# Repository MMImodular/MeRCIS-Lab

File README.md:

# MeRCIS Lab
##### Contributors: Matt Gaines, Joe Cressman, Jason Paximadas
___
This repository will be used to keep files up to date without dealing with Google Drive permissions.
The primary use case for now is maintaining a standard Eagle Library for future designs, but more will appear in time.

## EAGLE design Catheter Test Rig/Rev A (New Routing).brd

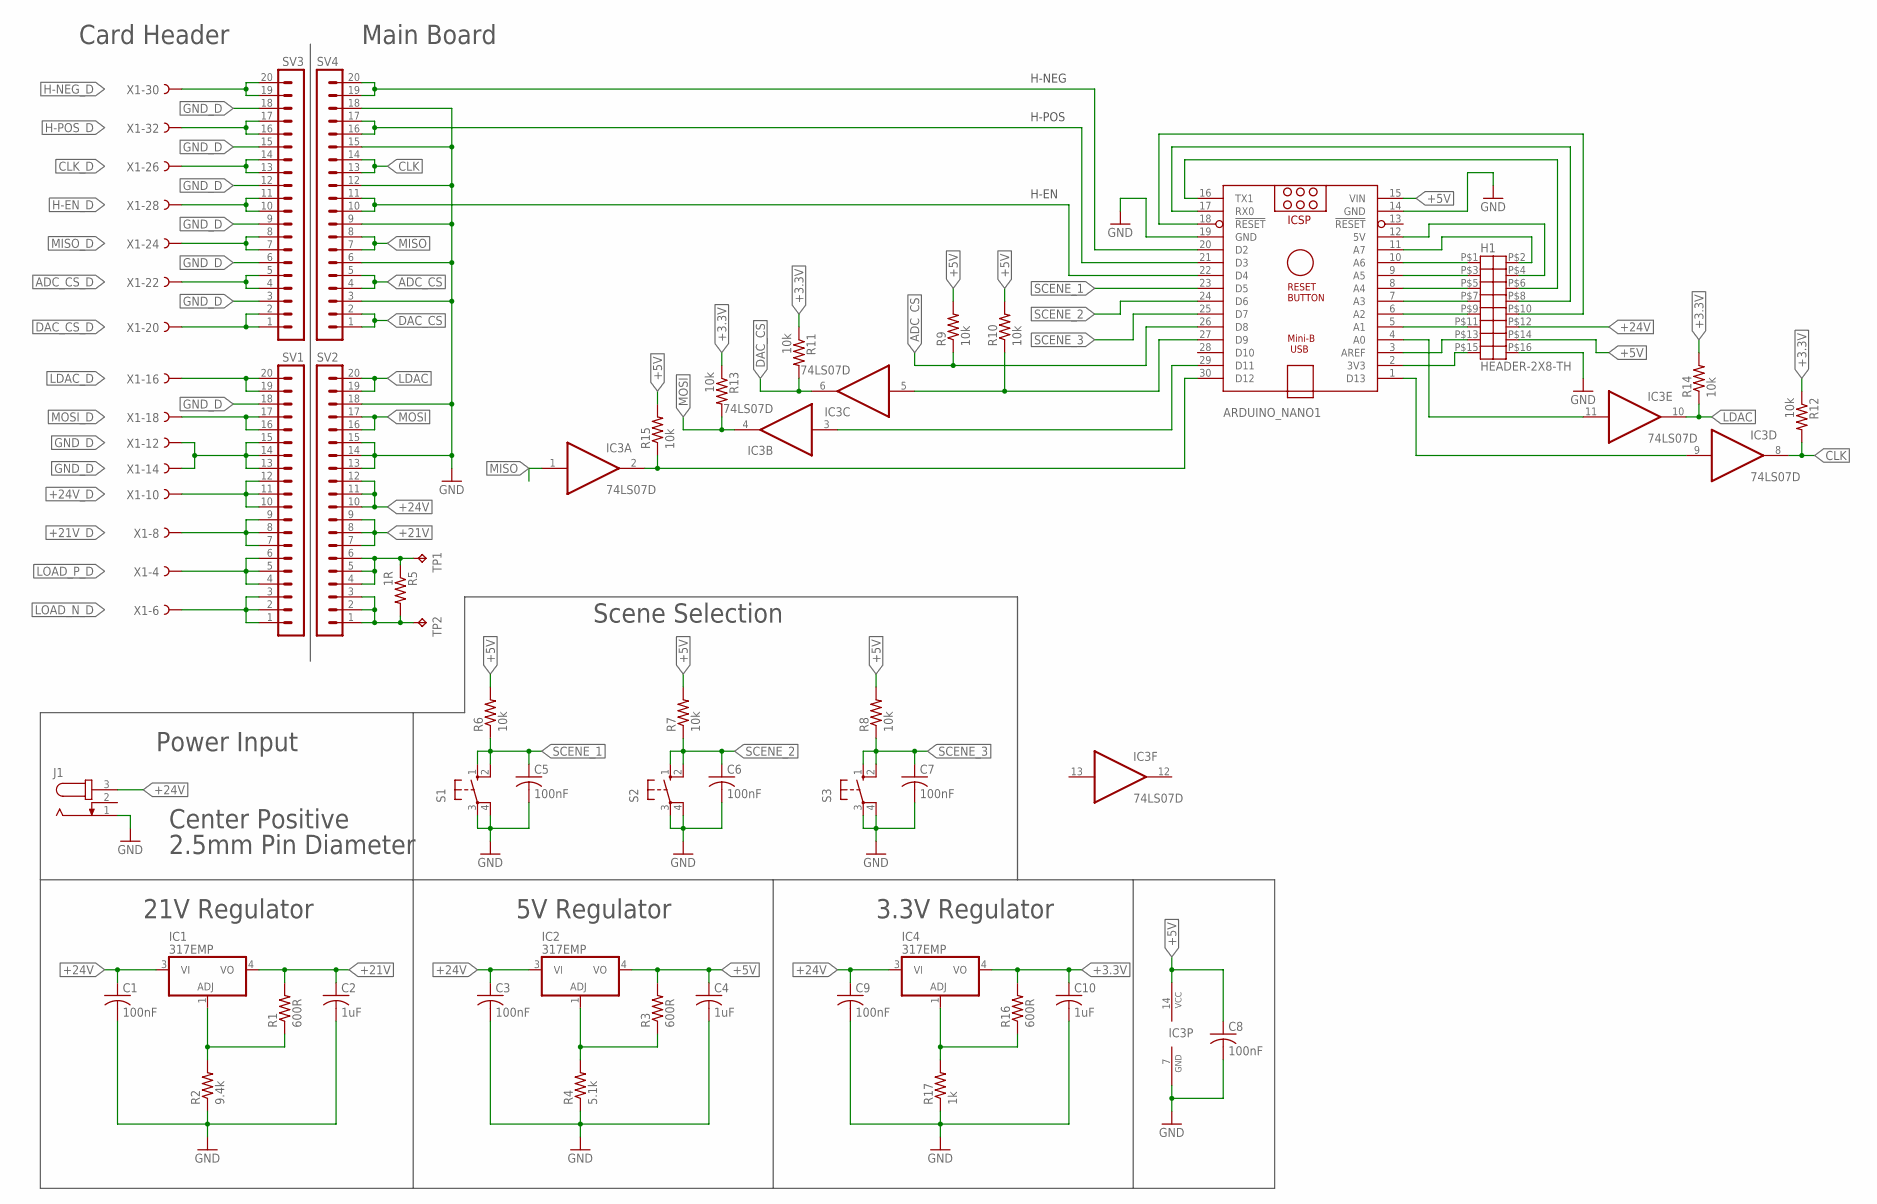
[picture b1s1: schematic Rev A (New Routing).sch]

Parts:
ARDUINO_NANO1: ARDUINO_NANO
C1, C3, C5, C6, C7, C8, C9: 100nF; C0603
C2, C4, C10: 1uF; C1206
H1: HEADER-2X8-TH
IC1, IC2, IC4: 317EMP; SOT223
IC3: 74LS07D; SO14
J1: JACK-PLUG1; SPC4078
R1, R3, R16: 600R; R0603
R2: 9.4k; R0603
R4: 5.1k; R0603
R5: 1R; R1206
R6, R7, R8, R9, R10, R11, R12, R13, R14, R15: 10k; R0603
R17: 1k; R0603
S1, S2, S3: 10-XX; B3F-10XX
SV1, SV3: MA20-1
SV2, SV4: MA20-1W
TP1, TP2: TPB2,54; B2,54
X1: FH15

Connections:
+3.3V: C10.1, IC4.4 (VO), R11.1, R12.1, R13.1, R14.2, R16.2
+5V: ARDUINO_NANO1.15 (VIN), C4.1, C8.1, H1.P$14, IC2.4 (VO), IC3.14 (VCC), R3.2, R6.2, R7.2, R8.2, R9.2, R10.2, R15.2
+21V: C2.1, IC1.4 (VO), R1.2, SV2.7, SV2.8, SV2.9
+21V_D: SV1.7, SV1.8, SV1.9, X1.8
+24V: C1.1, C3.1, C9.1, H1.P$12, IC1.3 (VI), IC2.3 (VI), IC4.3 (VI), J1.3, SV2.10, SV2.11, SV2.12
+24V_D: SV1.10, SV1.11, SV1.12, X1.10
ADC_CS: ARDUINO_NANO1.26 (D8), R9.1, SV4.4, SV4.5
ADC_CS_D: SV3.4, SV3.5, X1.22
CLK: IC3.8 (O), R12.2, SV4.13, SV4.14
CLK_D: SV3.13, SV3.14, X1.26
DAC_CS: IC3.6 (O), R11.2, SV4.1, SV4.2
DAC_CS_D: SV3.1, SV3.2, X1.20
GND: ARDUINO_NANO1.14 (GND), ARDUINO_NANO1.19 (GND), C1.2, C2.2, C3.2, C4.2, C5.2, C6.2, C7.2, C8.2, C9.2, C10.2, H1.P$16, IC3.7 (GND), J1.1, R2.1, R4.1, R17.1, S1.3, S1.4 (P1), S2.3, S2.4 (P1), S3.3, S3.4 (P1), SV2.13, SV2.14, SV2.15, SV2.18, SV4.3, SV4.6, SV4.9, SV4.12, SV4.15, SV4.18
GND_D: SV1.13, SV1.14, SV1.15, SV1.18, SV3.3, SV3.6, SV3.9, SV3.12, SV3.15, SV3.18, X1.12, X1.14
H-EN_D: SV3.10, SV3.11, X1.28
H-NEG_D: SV3.19, SV3.20, X1.30
H-POS_D: SV3.16, SV3.17, X1.32
LDAC: IC3.10 (O), R14.1, SV2.19, SV2.20
LDAC_D: SV1.19, SV1.20, X1.16
LOAD_N_D: SV1.1, SV1.2, SV1.3, X1.6
LOAD_P_D: SV1.4, SV1.5, SV1.6, X1.4
MISO: IC3.1 (I), SV4.7, SV4.8
MISO_D: SV3.7, SV3.8, X1.24
MOSI: IC3.4 (O), R13.2, SV2.16, SV2.17
MOSI_D: SV1.16, SV1.17, X1.18
unnamed: IC2.1 (ADJ), R3.1, R4.2
unnamed: IC1.1 (ADJ), R1.1, R2.2
unnamed: ARDUINO_NANO1.20 (D2), SV4.19, SV4.20
unnamed: ARDUINO_NANO1.2 (3V3), H1.P$15
unnamed: ARDUINO_NANO1.21 (D3), SV4.16, SV4.17
unnamed: ARDUINO_NANO1.3 (AREF), H1.P$13
unnamed: ARDUINO_NANO1.5 (A1), H1.P$11
unnamed: ARDUINO_NANO1.6 (A2), H1.P$9
unnamed: ARDUINO_NANO1.22 (D4), SV4.10, SV4.11
unnamed: ARDUINO_NANO1.7 (A3), H1.P$7
unnamed: ARDUINO_NANO1.8 (A4), H1.P$5
unnamed: ARDUINO_NANO1.9 (A5), H1.P$3
unnamed: ARDUINO_NANO1.10 (A6), H1.P$1
unnamed: ARDUINO_NANO1.11 (A7), H1.P$2
unnamed: ARDUINO_NANO1.12 (5V), H1.P$4
unnamed: ARDUINO_NANO1.16 (TX1), H1.P$6
unnamed: ARDUINO_NANO1.17 (RX0), H1.P$8
unnamed: ARDUINO_NANO1.18 (!RESET), H1.P$10
unnamed: ARDUINO_NANO1.27 (D9), IC3.5 (I), R10.1
unnamed: ARDUINO_NANO1.1 (D13), IC3.9 (I)
unnamed: ARDUINO_NANO1.29 (D11), IC3.3 (I)
unnamed: R5.1, SV2.4, SV2.5, SV2.6, TP1.TP
unnamed: R5.2, SV2.1, SV2.2, SV2.3, TP2.TP
unnamed: ARDUINO_NANO1.4 (A0), IC3.11 (I)
unnamed: ARDUINO_NANO1.30 (D12), IC3.2 (O), R15.1
unnamed: IC4.1 (ADJ), R16.1, R17.2
SCENE_1: ARDUINO_NANO1.23 (D5), C5.1, R6.1, S1.1 (S), S1.2 (S1)
SCENE_2: ARDUINO_NANO1.24 (D6), C6.1, R7.1, S2.1 (S), S2.2 (S1)
SCENE_3: ARDUINO_NANO1.25 (D7), C7.1, R8.1, S3.1 (S), S3.2 (S1)

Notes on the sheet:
Card Header
Power Input
Center Positive
2.5mm Pin Diameter
21V Regulator
Main Board
5V Regulator
Scene Selection
H-EN
H-POS
H-NEG
3.3V Regulator

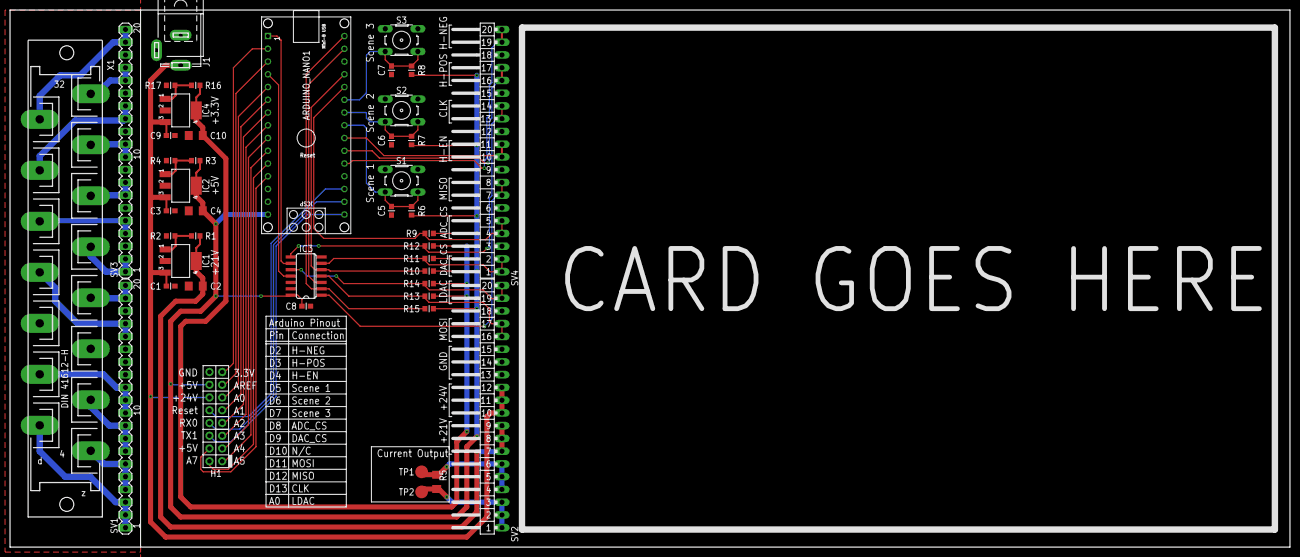
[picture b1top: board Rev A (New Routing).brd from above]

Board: 2 copper layers, 255.0 x 107.0 mm, 44 parts (0 on the bottom side), 54 nets.

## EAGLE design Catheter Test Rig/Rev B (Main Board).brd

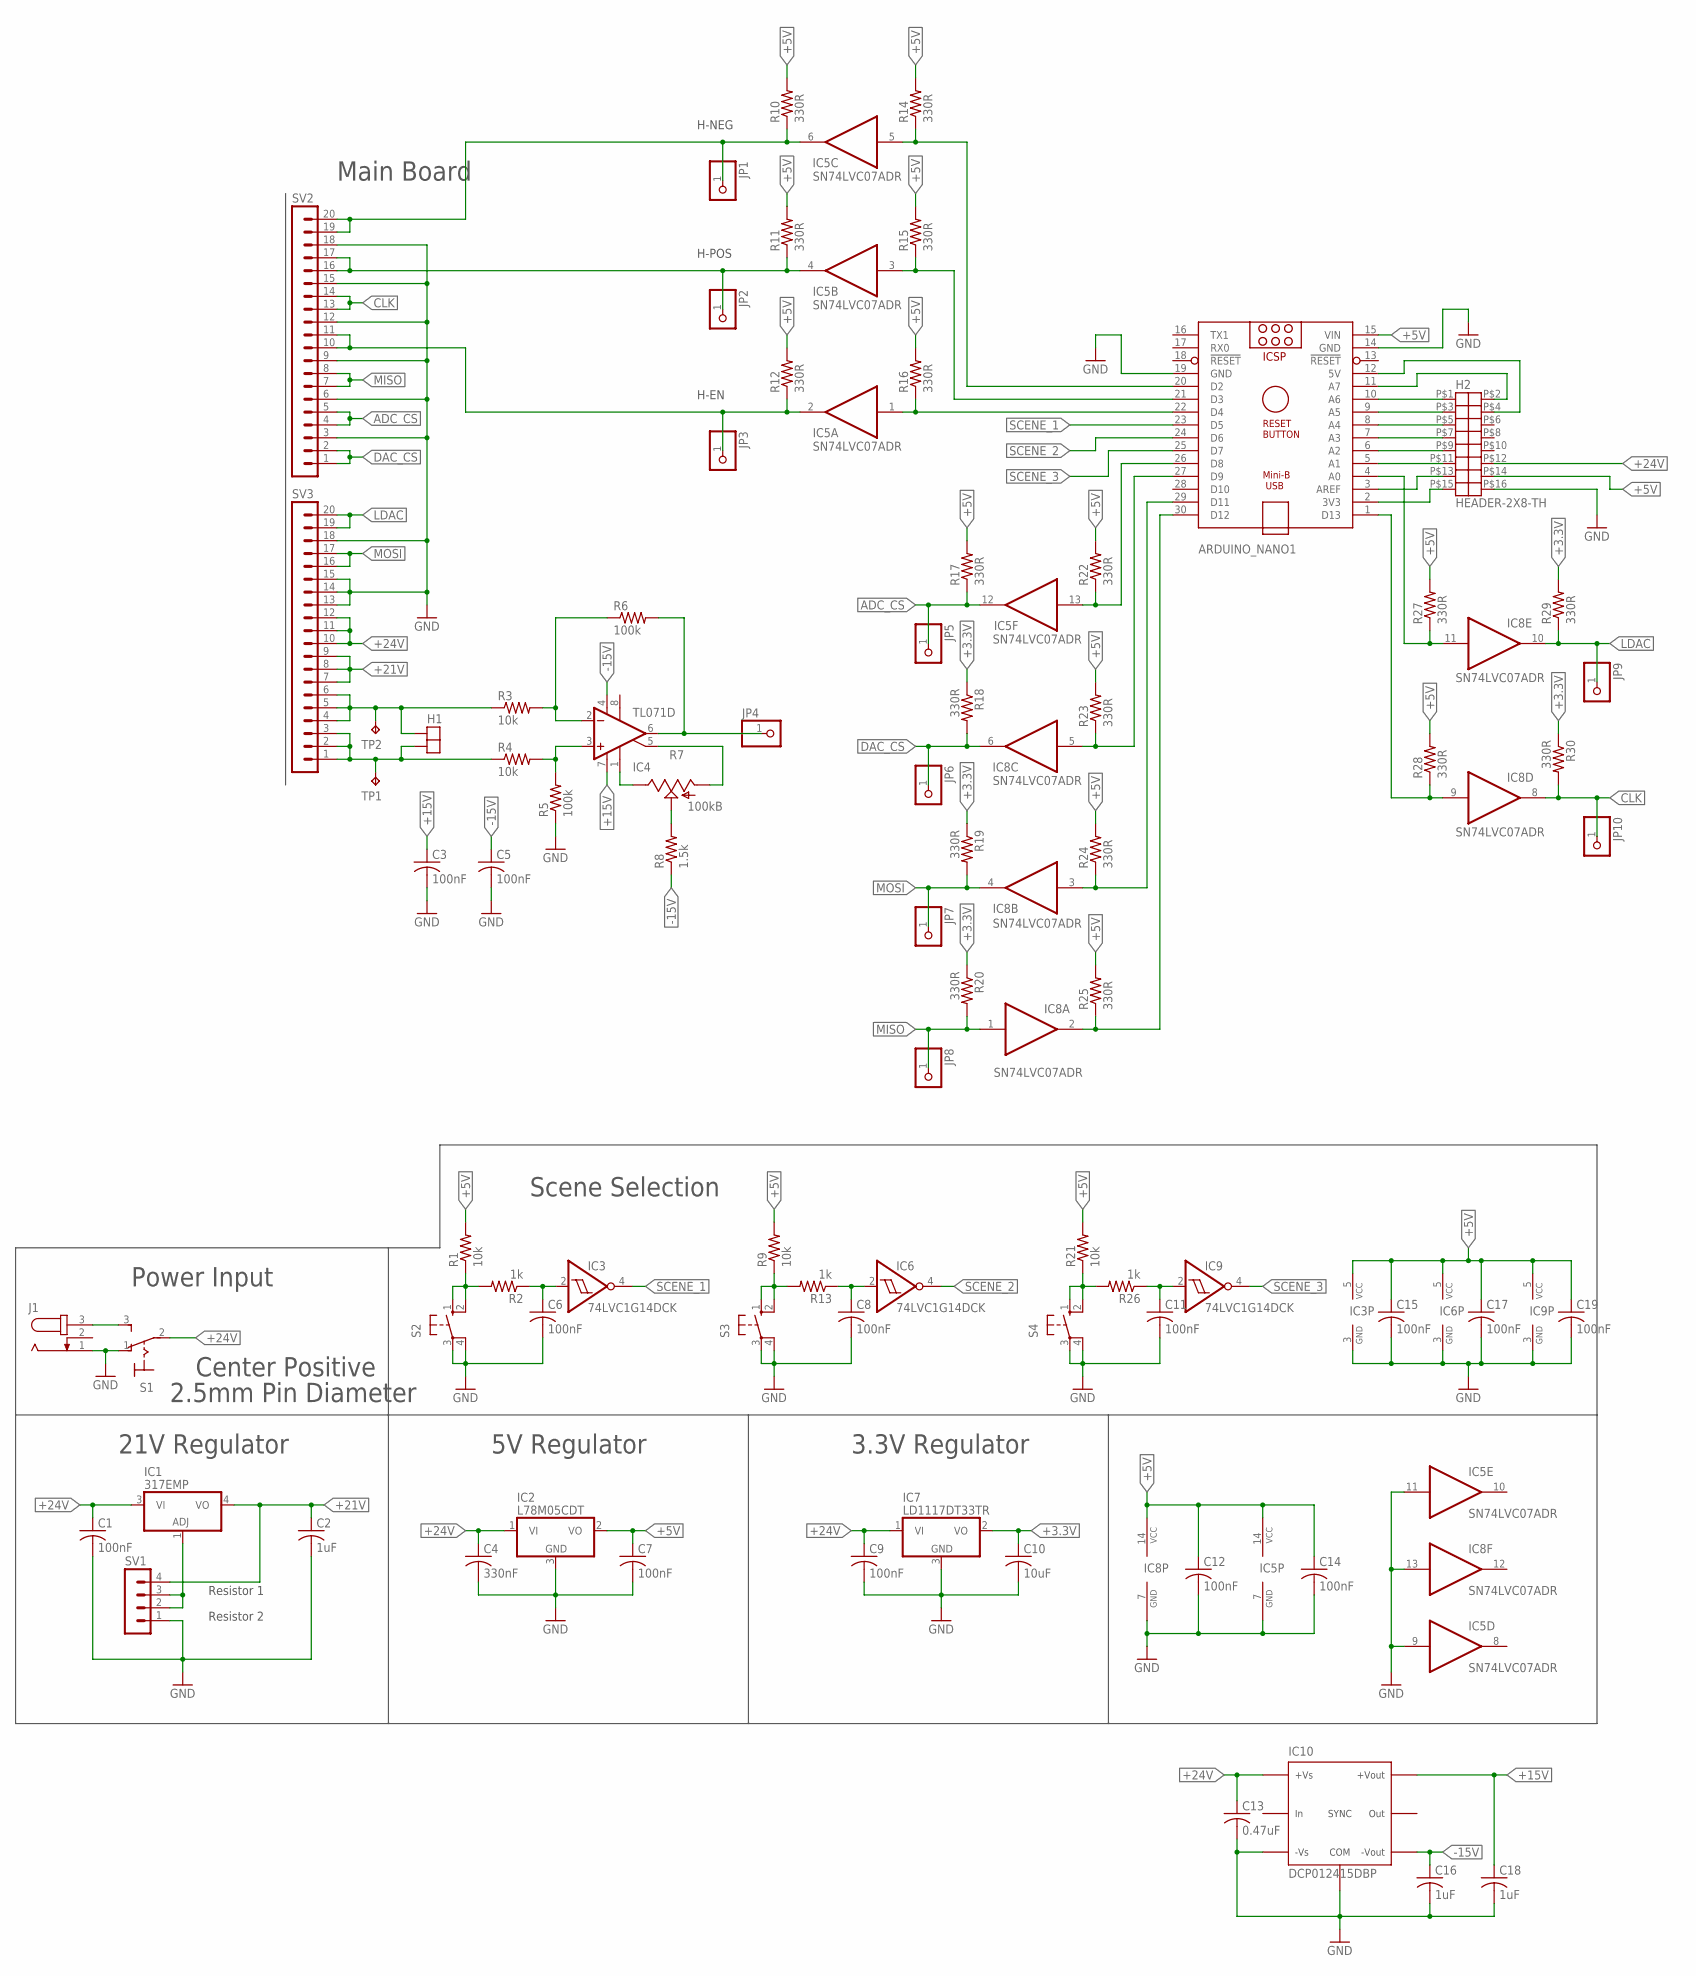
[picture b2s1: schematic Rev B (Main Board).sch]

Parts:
ARDUINO_NANO1: ARDUINO_NANO
C1, C3, C5, C6, C7, C8, C9, C11, C12, C14, C15, C17, C19: 100nF; C0805
C2, C16, C18: 1uF; C0805
C4: 330nF; C0805
C10: 10uF; C0805
C13: 0.47uF; C0805
H1: HEADER-1X2; HEADER-1X2-TH
H2: HEADER-2X8-TH
IC1: 317EMP; SOT223
IC2: L78M05CDT; TO252
IC3, IC6, IC9: 74LVC1G14DCK; SC70-5
IC4: TL071D; SO08
IC5, IC8: SN74LVC07ADR; SO14
IC7: LD1117DT33TR; TO252
IC10: DCP012415DBP; 7-PDIP
J1: JACK-PLUG1; SPC4078
JP1, JP2, JP3, JP4, JP5, JP6, JP7, JP8, JP9, JP10: PINHD-1X1; 1X01
R1, R3, R4, R9, R21: 10k; R0805
R2, R13, R26: 1k; R0805
R5, R6: 100k; R0805
R7: 100kB; RJ9W
R8: 1.5k; R0805
R10, R11, R12, R14, R15, R16, R17, R18, R19, R20, R22, R23, R24, R25, R27, R28, R29, R30: 330R; R0805
S1: 320-916
S2, S3, S4: 10-XX; B3F-10XX
SV1: MA04-1
SV2, SV3: MA20-1W
TP1, TP2: TPB2,54; B2,54

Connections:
+3.3V: C10.1, IC7.2 (VO), R18.1, R19.1, R20.1, R29.2, R30.1
+5V: ARDUINO_NANO1.15 (VIN), C7.1, C12.1, C14.1, C15.1, C17.1, C19.1, H2.P$14, IC2.2 (VO), IC3.5 (VCC), IC5.14 (VCC), IC6.5 (VCC), IC8.14 (VCC), IC9.5 (VCC), R1.2, R9.2, R10.2, R11.2, R12.2, R14.2, R15.2, R16.2, R17.2, R21.2, R22.2, R23.2, R24.2, R25.2, R27.2, R28.2
+15V: C3.1, C18.1, IC4.7 (V+), IC10.P$4
+21V: C2.1, IC1.4 (VO), SV1.4, SV3.7, SV3.8, SV3.9
+24V: C1.1, C4.1, C9.1, C13.1, H2.P$12, IC1.3 (VI), IC2.1 (VI), IC7.1 (VI), IC10.P$1, S1.2, SV3.10, SV3.11, SV3.12
-15V: C5.1, C16.1, IC4.4 (V-), IC10.P$5, R8.1
ADC_CS: IC5.12 (O), JP5.1, R17.1, SV2.4, SV2.5
CLK: IC8.8 (O), JP10.1, R30.2, SV2.13, SV2.14
DAC_CS: IC8.6 (O), JP6.1, R18.2, SV2.1, SV2.2
GND: ARDUINO_NANO1.14 (GND), ARDUINO_NANO1.19 (GND), C1.2, C2.2, C3.2, C4.2, C5.2, C6.2, C7.2, C8.2, C9.2, C10.2, C11.2, C12.2, C13.2, C14.2, C15.2, C16.2, C17.2, C18.2, C19.2, H2.P$16, IC2.3 (GND), IC3.3 (GND), IC5.7 (GND), IC5.9 (I), IC5.11 (I), IC6.3 (GND), IC7.3 (GND), IC8.7 (GND), IC8.13 (I), IC9.3 (GND), IC10.P$2, IC10.P$3, J1.1, R5.1, S1.1 (O), S2.3, S2.4 (P1), S3.3, S3.4 (P1), S4.3, S4.4 (P1), SV1.1, SV2.3, SV2.6, SV2.9, SV2.12, SV2.15, SV2.18, SV3.13, SV3.14, SV3.15, SV3.18
LDAC: IC8.10 (O), JP9.1, R29.1, SV3.19, SV3.20
MISO: IC8.1 (I), JP8.1, R20.2, SV2.7, SV2.8
MOSI: IC8.4 (O), JP7.1, R19.2, SV3.16, SV3.17
unnamed: IC5.2 (O), JP3.1, R12.1, SV2.10, SV2.11
unnamed: IC4.2 (-IN), R3.2, R6.1
unnamed: J1.3, S1.3 (S)
unnamed: ARDUINO_NANO1.2 (3V3), H2.P$15
unnamed: ARDUINO_NANO1.21 (D3), IC5.3 (I), R15.1
unnamed: ARDUINO_NANO1.3 (AREF), H2.P$13
unnamed: ARDUINO_NANO1.5 (A1), H2.P$11
unnamed: ARDUINO_NANO1.6 (A2), H2.P$9
unnamed: ARDUINO_NANO1.22 (D4), IC5.1 (I), R16.1
unnamed: ARDUINO_NANO1.7 (A3), H2.P$7
unnamed: ARDUINO_NANO1.8 (A4), H2.P$5
unnamed: ARDUINO_NANO1.9 (A5), H2.P$3
unnamed: ARDUINO_NANO1.10 (A6), H2.P$1
unnamed: ARDUINO_NANO1.11 (A7), H2.P$2
unnamed: ARDUINO_NANO1.12 (5V), H2.P$4
unnamed: ARDUINO_NANO1.27 (D9), IC8.5 (I), R23.1
unnamed: ARDUINO_NANO1.1 (D13), IC8.9 (I), R28.1
unnamed: ARDUINO_NANO1.29 (D11), IC8.3 (I), R24.1
unnamed: H1.P$1, R3.1, SV3.4, SV3.5, SV3.6, TP2.TP
unnamed: H1.P$2, R4.1, SV3.1, SV3.2, SV3.3, TP1.TP
unnamed: ARDUINO_NANO1.4 (A0), IC8.11 (I), R27.1
unnamed: ARDUINO_NANO1.30 (D12), IC8.2 (O), R25.1
unnamed: IC5.4 (O), JP2.1, R11.1, SV2.16, SV2.17
unnamed: R1.1, R2.2, S2.1 (S), S2.2 (S1)
unnamed: C6.1, IC3.2 (I), R2.1
unnamed: R9.1, R13.2, S3.1 (S), S3.2 (S1)
unnamed: C8.1, IC6.2 (I), R13.1
unnamed: R21.1, R26.2, S4.1 (S), S4.2 (S1)
unnamed: C11.1, IC9.2 (I), R26.1
unnamed: IC1.1 (ADJ), SV1.2, SV1.3
unnamed: ARDUINO_NANO1.20 (D2), IC5.5 (I), R14.1
unnamed: ARDUINO_NANO1.26 (D8), IC5.13 (I), R22.1
unnamed: IC5.6 (O), JP1.1, R10.1, SV2.19, SV2.20
unnamed: IC4.3 (+IN), R4.2, R5.2
unnamed: IC4.6 (OUT), JP4.1, R6.2
unnamed: IC4.1 (ON1), R7.E
unnamed: IC4.5 (ON2), R7.A
unnamed: R7.S, R8.2
SCENE_1: ARDUINO_NANO1.23 (D5), IC3.4 (O)
SCENE_2: ARDUINO_NANO1.24 (D6), IC6.4 (O)
SCENE_3: ARDUINO_NANO1.25 (D7), IC9.4 (O)

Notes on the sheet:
Power Input
Center Positive
2.5mm Pin Diameter
21V Regulator
Main Board
5V Regulator
Scene Selection
H-EN
H-POS
H-NEG
3.3V Regulator
Resistor 1
Resistor 2

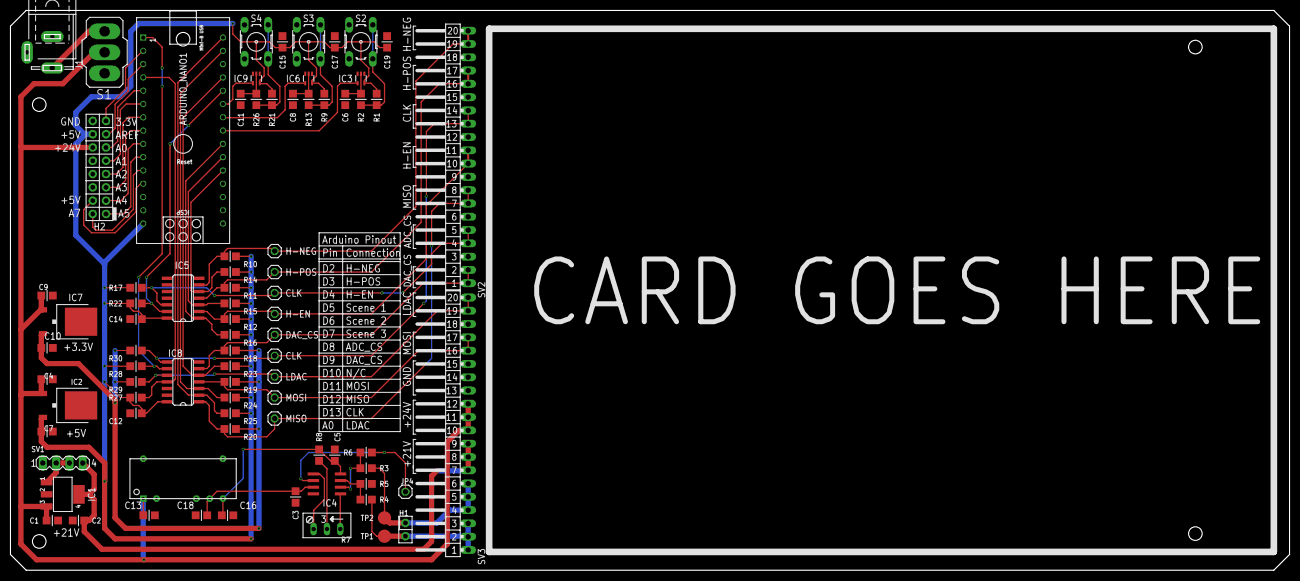
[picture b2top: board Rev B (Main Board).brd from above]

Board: 2 copper layers, 244.5 x 107.0 mm, 82 parts (0 on the bottom side), 54 nets.

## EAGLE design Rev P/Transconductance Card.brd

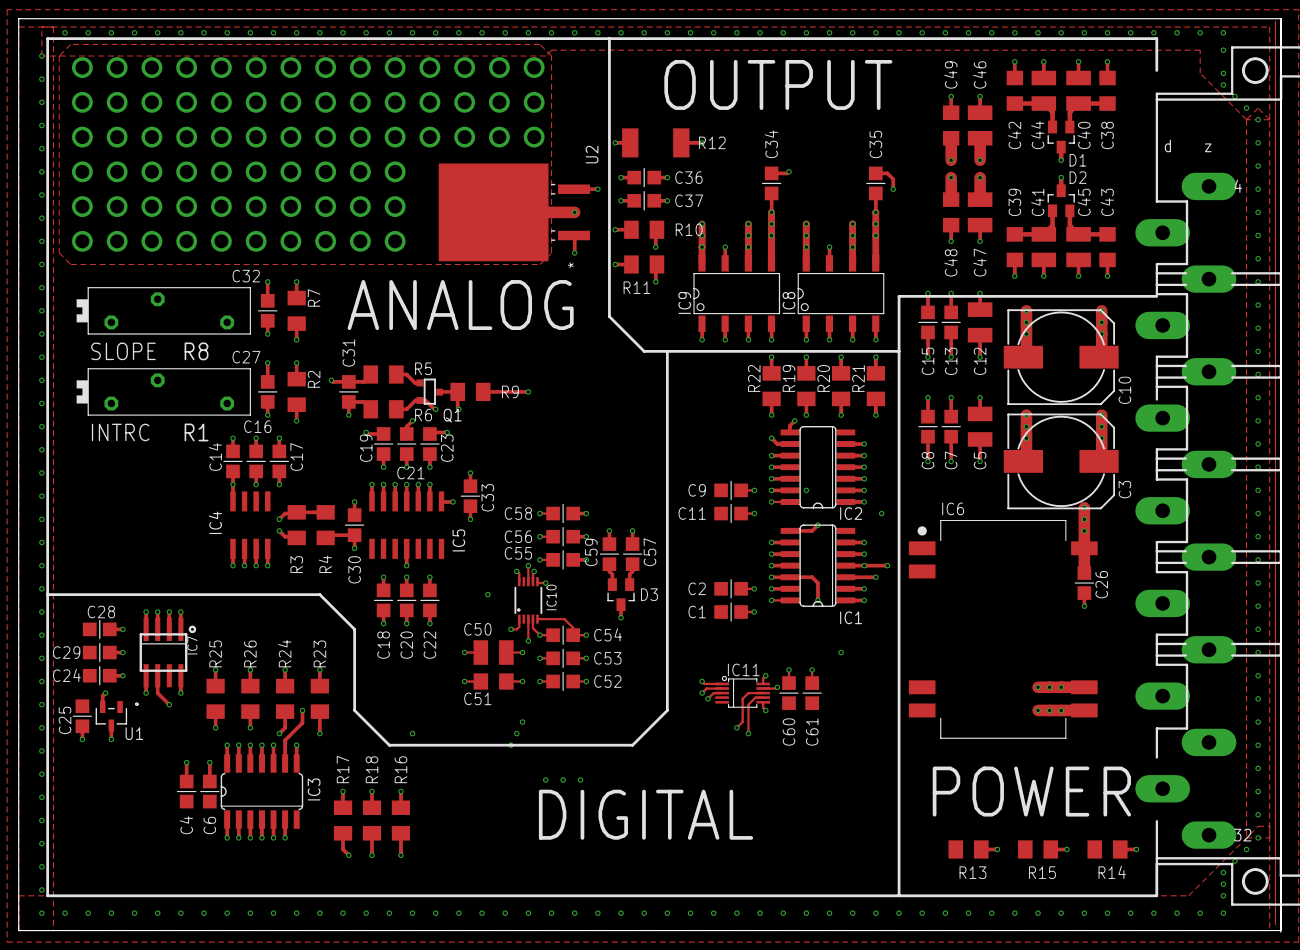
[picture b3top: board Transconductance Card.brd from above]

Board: 4 copper layers, 138.4 x 100.0 mm, 105 parts (0 on the bottom side), 58 nets.

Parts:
C1, C4, C7, C9, C13, C17, C18, C19, C24, C25, C52, C55, C60: 1u; C0805
C2, C6, C8, C11, C15, C16, C20, C21, C26, C27, C28, C30, C32, C34, C36, C53, C56, C57, C61: 0.1u; C0805
C3, C10: 470u; 140CLH-1010
C5, C12: 10u; C1210
C14, C22, C23, C31, C33, C54, C58: 0.01u; C0805
C29: 10u; C0805
C35, C37, C59: 1n; C0805
C38, C39, C42, C43, C48, C49, C51: 1n; C1206
C40, C41, C44, C45, C46, C47, C50: 0.1u; C1210
D1, D2, D3: BAS70-04; SOT23
IC1, IC2: 74LS00; 74XX-US_SO14:1
IC3: 74LS07D; SO14
IC4: TLC272D; SO08
IC5: OP484; SO14
IC6: SF_ISC03_DC_DC16-SMD; SF_ISC03_SOP254P1879X863-16N
IC7: SO-8
IC8, IC9: ASSR-1530; ASSR-1530_SO8
IC10: LT1991MS; MSOP10
IC11: ADS8319; VSSOP-10
Q1: 2N7000; SOT-23
R1: 20k; PT-SPIN
R2: 100k; M1206
R3: 220; M1206
R4, R6, R9, R10, R25: 1k; M1206
R5, R11: 100ohm; M1206
R7: 9.1k; M1206
R8: 5k; PT-SPIN
R12: 1ohm; R2512
R13, R14, R15, R16, R17, R18: 10k; M1206
R19, R20, R21, R22, R23, R24: 330; M1206
R26: 2k; M1206
U1: MCP1700T-3302E/TT; SOT-23_MC
U2: IRF9Z24NPbF; UL_IRF9Z24_D2PAK
X1: H15MLE; H15ML

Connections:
1: IC1.4, IC1.5, IC1.9, IC3.6, R17.2
2: IC1.1, IC1.2, IC1.13, IC3.4, R18.2
3: IC1.10, IC1.12, IC2.9, IC2.12, IC3.2, R16.2
3&1: IC8.2, R20.1
3&2: IC8.4, R21.1
+3.3V: C24.1, C28.1, C29.1, IC7.P$3, IC7.P$8, R26.1, U1.2
+5V: C1.1, C2.1, C4.1, C6.1, C9.1, C11.1, C14.1, C16.1, C17.1, C25.1, C60.1, C61.1, IC1.14, IC2.14, IC3.14, IC4.8, IC6.9, IC8.1, IC8.3, IC9.1, IC9.3, IC11.1, IC11.2, IC11.9, IC11.10, R1.1, R16.1, R17.1, R18.1, R23.2, R24.2, R25.1, U1.3
+20V: C10.+, C12.1, C13.1, C15.1, C50.1, C51.1, IC10.1, IC10.3, R9.2, R12.2, X1.Z8
+24V: C3.+, C5.1, C7.1, C8.1, C18.1, C20.1, C22.1, C26.1, C55.1, C56.1, C58.1, IC5.4, IC6.16, IC10.7, X1.D10
-5V: C19.2, C21.2, C23.2, C27.2, C52.2, C53.2, C54.2, IC5.11, IC6.10, IC10.4, R1.2
ADC-CS: IC3.9, X1.D22
AGND: C3.-, C5.2, C7.2, C8.2, C10.-, C12.2, C13.2, C14.2, C15.2, C16.2, C17.2, C18.2, C19.1, C20.2, C21.1, C22.2, C23.1, C26.2, C30.2, C32.2, C34.2, C35.2, C36.2, C37.2, C38.2, C39.2, C40.2, C41.2, C42.2, C43.2, C44.2, C45.2, C46.2, C47.2, C48.2, C49.2, C50.2, C51.2, C52.1, C53.1, C54.1, C55.2, C56.2, C57.2, C58.2, C59.2, IC4.4, IC7.P$2, IC8.7, IC9.7, IC10.5, R8.1, X1.Z12
CLK: IC3.11, IC7.P$5, X1.D26
DAC-CS: IC7.P$4, X1.Z20
DGND: C1.2, C2.2, C4.2, C6.2, C9.2, C11.2, C24.2, C25.2, C28.2, C29.2, C60.2, C61.2, IC1.7, IC2.7, IC3.7, IC6.1, IC6.8, IC7.P$7, IC11.4, IC11.5, R13.1, R14.1, R15.1, U1.1, X1.D14
H-BDG: C34.1, C35.1, IC8.5, IC9.5, U2.2
H-EN: IC3.1, R13.2, X1.Z28
H-NEG: IC3.3, R15.2, X1.D30
H-POS: IC3.5, R14.2, X1.Z32
LOAD_N: C47.1, C48.1, D2.3, IC8.6, IC8.8, X1.D6
LOAD_P: C46.1, C49.1, D1.3, IC9.6, IC9.8, X1.Z4
LSENSE: C36.1, C37.1, IC10.8, IC10.10, R10.2, R12.1, U2.3
MISO: IC3.12, R26.2, X1.Z24
MOSI: IC7.P$6, X1.D18
unnamed: D3.3, IC10.6, IC11.3
unnamed: Q1.2, R6.1, R7.2
unnamed: IC3.8, IC11.6, R23.1
unnamed: IC3.10, IC11.8, R24.1
unnamed: Q1.1, R5.1
unnamed: IC1.6, IC2.10
unnamed: IC1.3, IC2.13
unnamed: IC3.13, IC11.7, R25.2
unnamed: C31.1, IC5.14, R5.2
unnamed: IC4.3, IC7.P$1
unnamed: IC5.10, Q1.3, R9.1
unnamed: R11.2, U2.1
unnamed: C31.2, IC5.13, R6.2
unnamed: C33.2, IC5.8, R11.1
unnamed: C38.1, C40.1, D1.1
unnamed: C30.1, IC5.12, R4.2
unnamed: C32.1, R7.1, R8.2, R8.3
unnamed: C33.1, IC5.9, R10.1
unnamed: C27.1, R1.3, R2.1
unnamed: C42.1, C44.1, D1.2
unnamed: IC1.8, IC2.4, IC2.5
unnamed: IC1.11, IC2.1, IC2.2
unnamed: IC2.8, R19.2
unnamed: IC2.6, R20.2
unnamed: IC2.3, R21.2
unnamed: IC4.1, R3.2, R4.1
unnamed: IC2.11, R22.2
unnamed: C39.1, C41.1, D2.1
unnamed: C43.1, C45.1, D2.2
unnamed: C57.1, D3.1
unnamed: C59.1, D3.2
unnamed: IC4.2, R2.2, R3.1
~3||1: IC9.4, R19.1
~3||2: IC9.2, R22.1

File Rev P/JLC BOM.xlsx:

Comment | Designator | Footprint | LCSC Part # | Column1
AD5551 | IC7 | SO-8 |  | pads good
0.01u | C14, C22, C23, C31, C33, C54, C58 | C0805 | C1710
0.1u | C40, C41, C44, C45, C46, C47, C50 | C1210 | C141218
0.1u | C2, C6, C8, C11, C15, C16, C20, C21, C26, C27, C28, C30, C32, C34, C36, C53, C5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 | C0805 | C49678
100k | R2 | M1206 | C17900
100ohm | R5, R11 | M1206 | C17901
10k | R13, R14, R15, R16, R17, R18 | M1206 | C17902
10u | C5, C12 | C1210 | C39232
10u | C29 | C0805 | C15850
1k | R4, R6, R9, R10, R25 | M1206 | C4410
1n | C38, C39, C42, C43, C48, C49, C51 | C1206 | C35216
1n | C35, C37, C59 | C0805 | C46653
1ohm | R12 | R2512 | C11254
1u | C1, C4, C7, C9, C13, C17, C18, C19, C24, C25, C52, C55, C60 | C0805 | C28323
20k | R1 | PT-SPIN
220 | R3 | M1206 | C17957
2N7000 | Q1 | SOT-23
2k | R26 | M1206 | C17944
330 | R19, R20, R21, R22, R23, R24 | M1206 | C17930
470u | C3, C10 | 140CLH-1010 | C3350
5k | R8 | PT-SPIN
74LS00 | IC1, IC2 | 74XX-US_SO14:1 | C74558 | NOTE: IC2 should be replaced with the SN7438 due to sink current requirements t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
74LS07D | IC3 | SO14 | C6801
9.1k | R7 | M1206 | C18025
ADS8319 | IC11 | VSSOP-10 |  | pads good
ASSR-1530 | IC8, IC9 | ASSR-1530_SO8
BAS70-04 | D1, D2, D3 | SOT23 | C134375
H15MLE | X1 | H15ML
IRF9Z24NPbF | U2 | UL_IRF9Z24_D2PAK | C169781
LT1991MS | IC10 | MSOP10 |  | EXTEND PADS FOR SOLDERING
MCP1700T-3302E/TT | U1 | SOT-23_MC | C39051
LM324D | IC5 | SO14 | C71035
SF_ISC03_DC_DC16-SMD | IC6 | SF_ISC03_SOP254P1879X863-16N
TLC272D | IC4 | SO08 | C6982

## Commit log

2021-01-06 Added new devices to library and Rev O.2 files
2021-01-12 Added/connected new ADC & DAC to schematic; still unrouted on board
2021-01-14 Added passives and some amplifiers
2021-01-18 Added Card Tester Files
2021-01-19 Imported Rev O components
2021-01-20 Added C0306 Footprint
2021-01-25 Made bypass capacitor-diode thing symmetrical
2021-02-06 Partial Board Routing
    Need to finish routing power and update schematic power/GND symbols to be consistent with new convention
2021-02-07 Routing Complete
    Still need to heat sink main fet and clean silk screen
2021-02-09 Board Routing Finished
    Need to clean up silkscreen still
2021-02-13 Cleaned up silk screen
2021-02-14 Created BOM for JLCPCB Assembly
2021-03-11 Update BOM
2021-05-26 Added Test Rig Arduino code
2021-07-27 Added new card tester firmware

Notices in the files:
Rev P/Transconductance Card.brd:
Copyright 2021, Matthew Gaines, MeRCIS LABS, CWRU
